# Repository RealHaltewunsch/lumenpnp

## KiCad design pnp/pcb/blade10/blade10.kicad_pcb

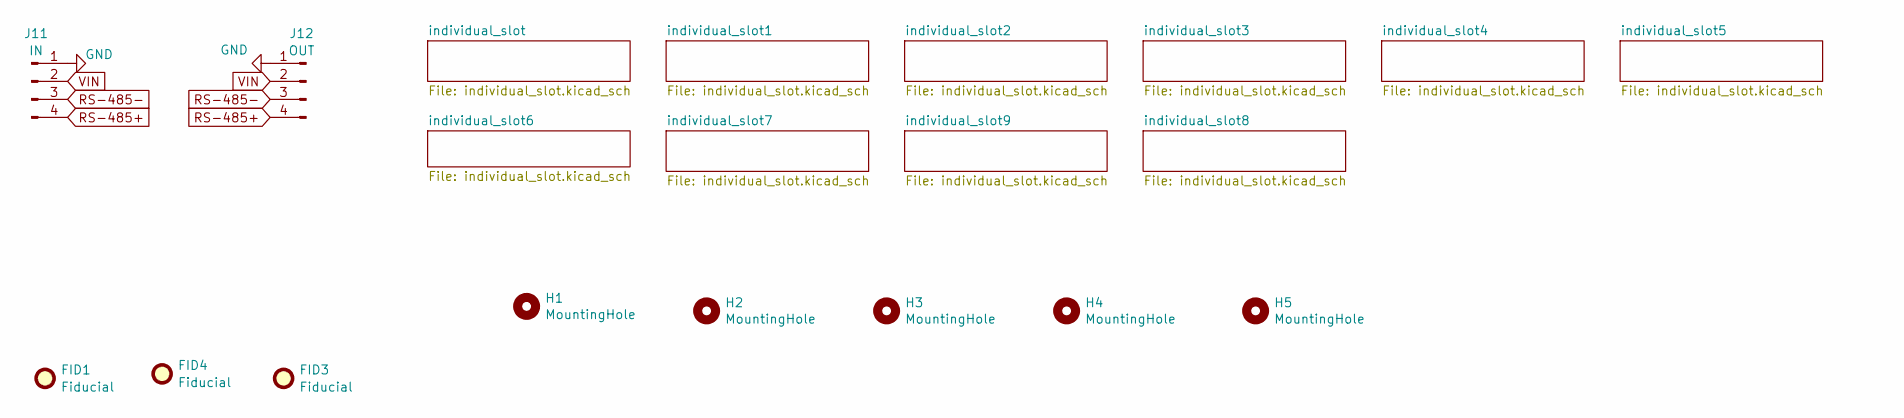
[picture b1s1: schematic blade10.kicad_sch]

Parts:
FID1, FID3, FID4: Fiducial; Fiducial_1mm_Mask2mm
H1, H2, H3, H4, H5: MountingHole; MountingHole_3.2mm_M3
J11: IN; JST_PH_B4B-PH-SM4-TB_1x04-1MP_P2.00mm_Vertical
J12: OUT; JST_PH_B4B-PH-SM4-TB_1x04-1MP_P2.00mm_Vertical

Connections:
GND: J11.1, J12.1; also elsewhere on the board
RS-485+: J11.4, J12.4; also elsewhere on the board
RS-485-: J11.3, J12.3; also elsewhere on the board
VIN: J11.2, J12.2; also elsewhere on the board

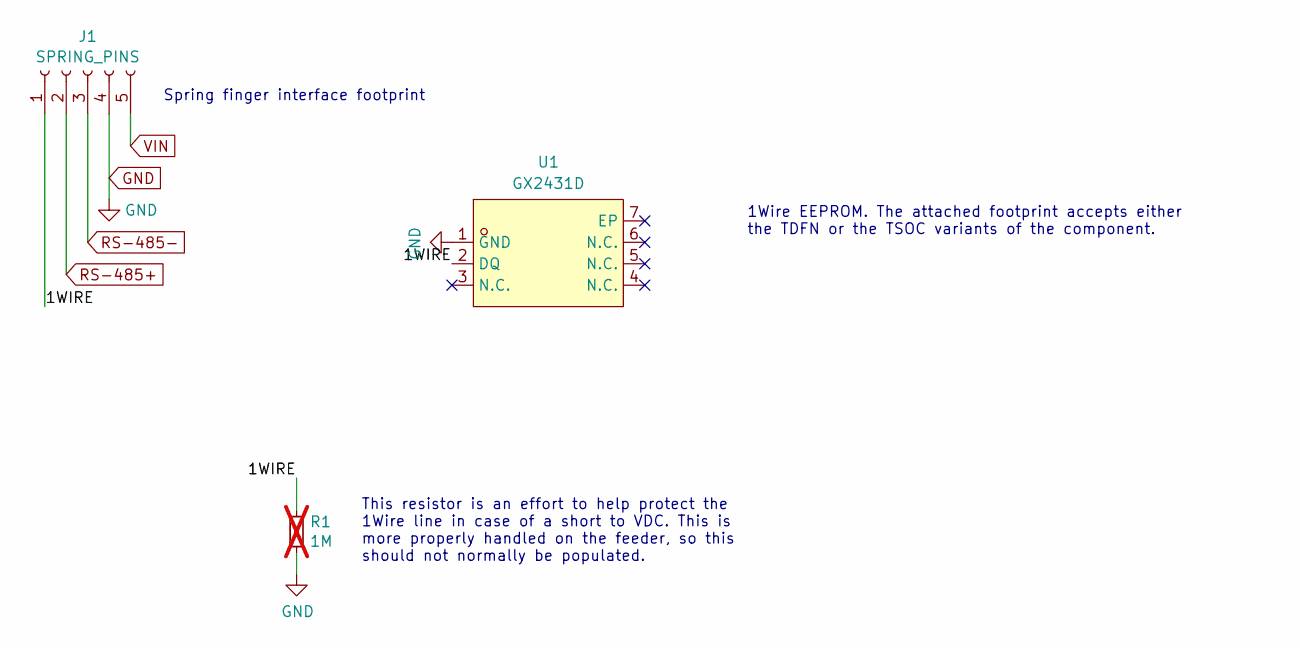
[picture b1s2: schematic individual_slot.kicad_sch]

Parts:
J1: SPRING_PINS; AVX-915-005-541-Contact-Surface
R1: 1M; R_0805_2012Metric; JLCPCB C17437; not fitted
U1: GX2431D; DFN-6_L4.0-W4.0-P1.0-TL-EP2.7; MPN GX2431D; LCSC Part C2758004

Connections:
/individual_slot/1WIRE: J1.1, R1.1, U1.2 (DQ)
GND: J1.4, R1.2, U1.1 (GND); also elsewhere on the board
RS-485+: J1.2; also elsewhere on the board
RS-485-: J1.3; also elsewhere on the board
VIN: J1.5; also elsewhere on the board

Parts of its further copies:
J2, J3, J4, J5, J6, J7, J8, J9, J10: SPRING_PINS; AVX-915-005-541-Contact-Surface
R2, R3, R4, R5, R6, R7, R8, R9, R10: 1M; R_0805_2012Metric; JLCPCB C17437; not fitted
U2, U3, U4, U5, U6, U7, U8, U9, U10: GX2431D; DFN-6_L4.0-W4.0-P1.0-TL-EP2.7; MPN GX2431D; LCSC Part C2758004

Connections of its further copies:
/individual_slot1/1WIRE: J2.1, R2.1, U2.2 (DQ)
/individual_slot2/1WIRE: J3.1, R3.1, U3.2 (DQ)
/individual_slot3/1WIRE: J4.1, R4.1, U4.2 (DQ)
/individual_slot4/1WIRE: J5.1, R5.1, U5.2 (DQ)
/individual_slot5/1WIRE: J6.1, R6.1, U6.2 (DQ)
/individual_slot6/1WIRE: J7.1, R7.1, U7.2 (DQ)
/individual_slot7/1WIRE: J8.1, R8.1, U8.2 (DQ)
/individual_slot8/1WIRE: J9.1, R9.1, U9.2 (DQ)
/individual_slot9/1WIRE: J10.1, R10.1, U10.2 (DQ)
GND: J2.4, J3.4, J4.4, J5.4, J6.4, J7.4, J8.4, J9.4, J10.4, R2.2, R3.2, R4.2, R5.2, R6.2, R7.2, R8.2, R9.2, R10.2, U2.1 (GND), U3.1 (GND), U4.1 (GND), U5.1 (GND), U6.1 (GND), U7.1 (GND), U8.1 (GND), U9.1 (GND), U10.1 (GND); also elsewhere on the board
RS-485+: J2.2, J3.2, J4.2, J5.2, J6.2, J7.2, J8.2, J9.2, J10.2; also elsewhere on the board
RS-485-: J2.3, J3.3, J4.3, J5.3, J6.3, J7.3, J8.3, J9.3, J10.3; also elsewhere on the board
VIN: J2.5, J3.5, J4.5, J5.5, J6.5, J7.5, J8.5, J9.5, J10.5; also elsewhere on the board

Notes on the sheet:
This resistor is an effort to help protect the 1Wire line in case of a short to VDC. This is more properly handled on the feeder, so this should not normally be populated.
Spring finger interface footprint
1Wire EEPROM. The attached footprint accepts either the TDFN or the TSOC variants of the component.

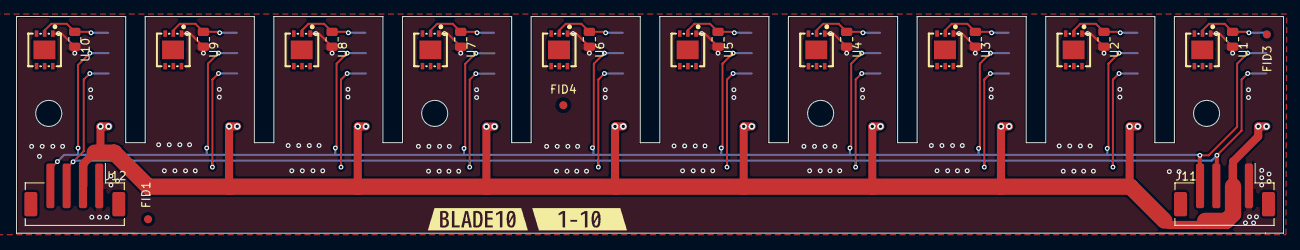
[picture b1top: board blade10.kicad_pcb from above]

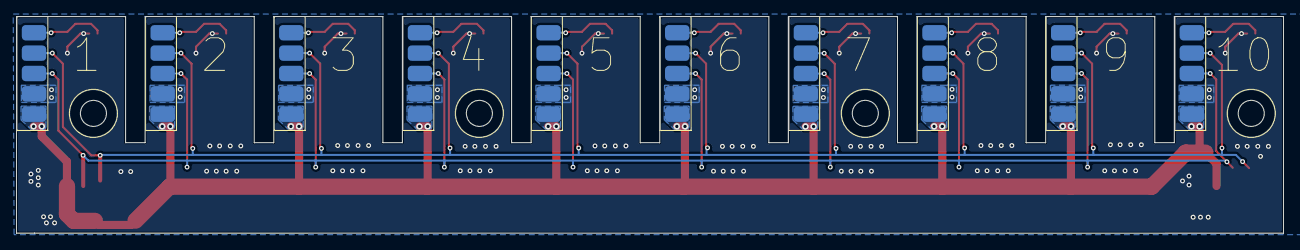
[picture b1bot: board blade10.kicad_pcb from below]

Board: 2 copper layers, 155.6 x 26.6 mm, 41 parts (10 on the bottom side), 14 nets.

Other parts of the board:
kibuzzard-6A89BB1D: G***; kibuzzard-6A89BB1D
kibuzzard-6A89BB85: G***; kibuzzard-6A89BB85

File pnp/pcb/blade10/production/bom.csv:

Designator,Footprint,Quantity,Value,LCSC Part #
"FID1, FID3, FID4",Fiducial_1mm_Mask2mm,3,Fiducial,
"H2, H3, H4, H5",MountingHole_3.2mm_M3,4,MountingHole,
"J1, J10, J2, J3, J4, J5, J6, J7, J8, J9",AVX-915-005-541-Contact-Surface,10,SPRING_PINS,
J11,JST_PH_B4B-PH-SM4-TB_1x04-1MP_P2.00mm_Vertical,1,IN,
J12,JST_PH_B4B-PH-SM4-TB_1x04-1MP_P2.00mm_Vertical,1,OUT,
"R1, R10, R2, R3, R4, R5, R6, R7, R8, R9",0805,10,1M,DNP
"U1, U10, U2, U3, U4, U5, U6, U7, U8, U9",DFN-6_L4.0-W4.0-P1.0-TL-EP2.7,10,GX2431D,C2758004
